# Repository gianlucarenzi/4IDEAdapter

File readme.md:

# Amiga 4 IDE Hard Parallel ATA Adapter
Created by Gianluca Renzi (C) 2019
E-Mail: <icjtqr@gmail.com>
<gianlucarenzi@eurek.it>

# What is it?
It is a simple but powerful adapter to use internally in any Amiga 1200 or Amiga 600 Computer installed in a tower-like case!
It must be connected to the IDE 44-pin interface on the motherboard to drive up to 4 ATA/ATAPI devices like Hard Drives, DVD Rom Drives and compatible drives.

This project follow the same DIY project in Aminet (search 4IDE in docs/hw) or simply check out here:

[Aminet 4IDE Readme](Aminet-4IDE/4IDE.readme)

# Software
[Aminet IDE97 Driver](http://aminet.net/driver/media/IDEfix97.lha)

[Aminet IDE97 Turbo Driver](http://aminet.net/driver/media/IDEfixTURBO.lha)

[Aminet IDE97 Patches](http://aminet.net/driver/media/IDEFix_patches.lha)

# Hardware Point-Of-View
This board has three indipendent activity leds, one for each channel. Moreover the activity leds are merged together in the motherboard so the HDD led nearby the floppy connector can be used as the only activity led.

# TODO
May be it can be useful to add a 90-degrees rise connector if the system has some sort of bus board, just to let this board flat as the motherboard.

# Images

# Whats changed?
V2.2 Added Aminet Stuff

# Licence
This entire project is available under the GNU General Public License v3 licence.
See licence.txt for more details.

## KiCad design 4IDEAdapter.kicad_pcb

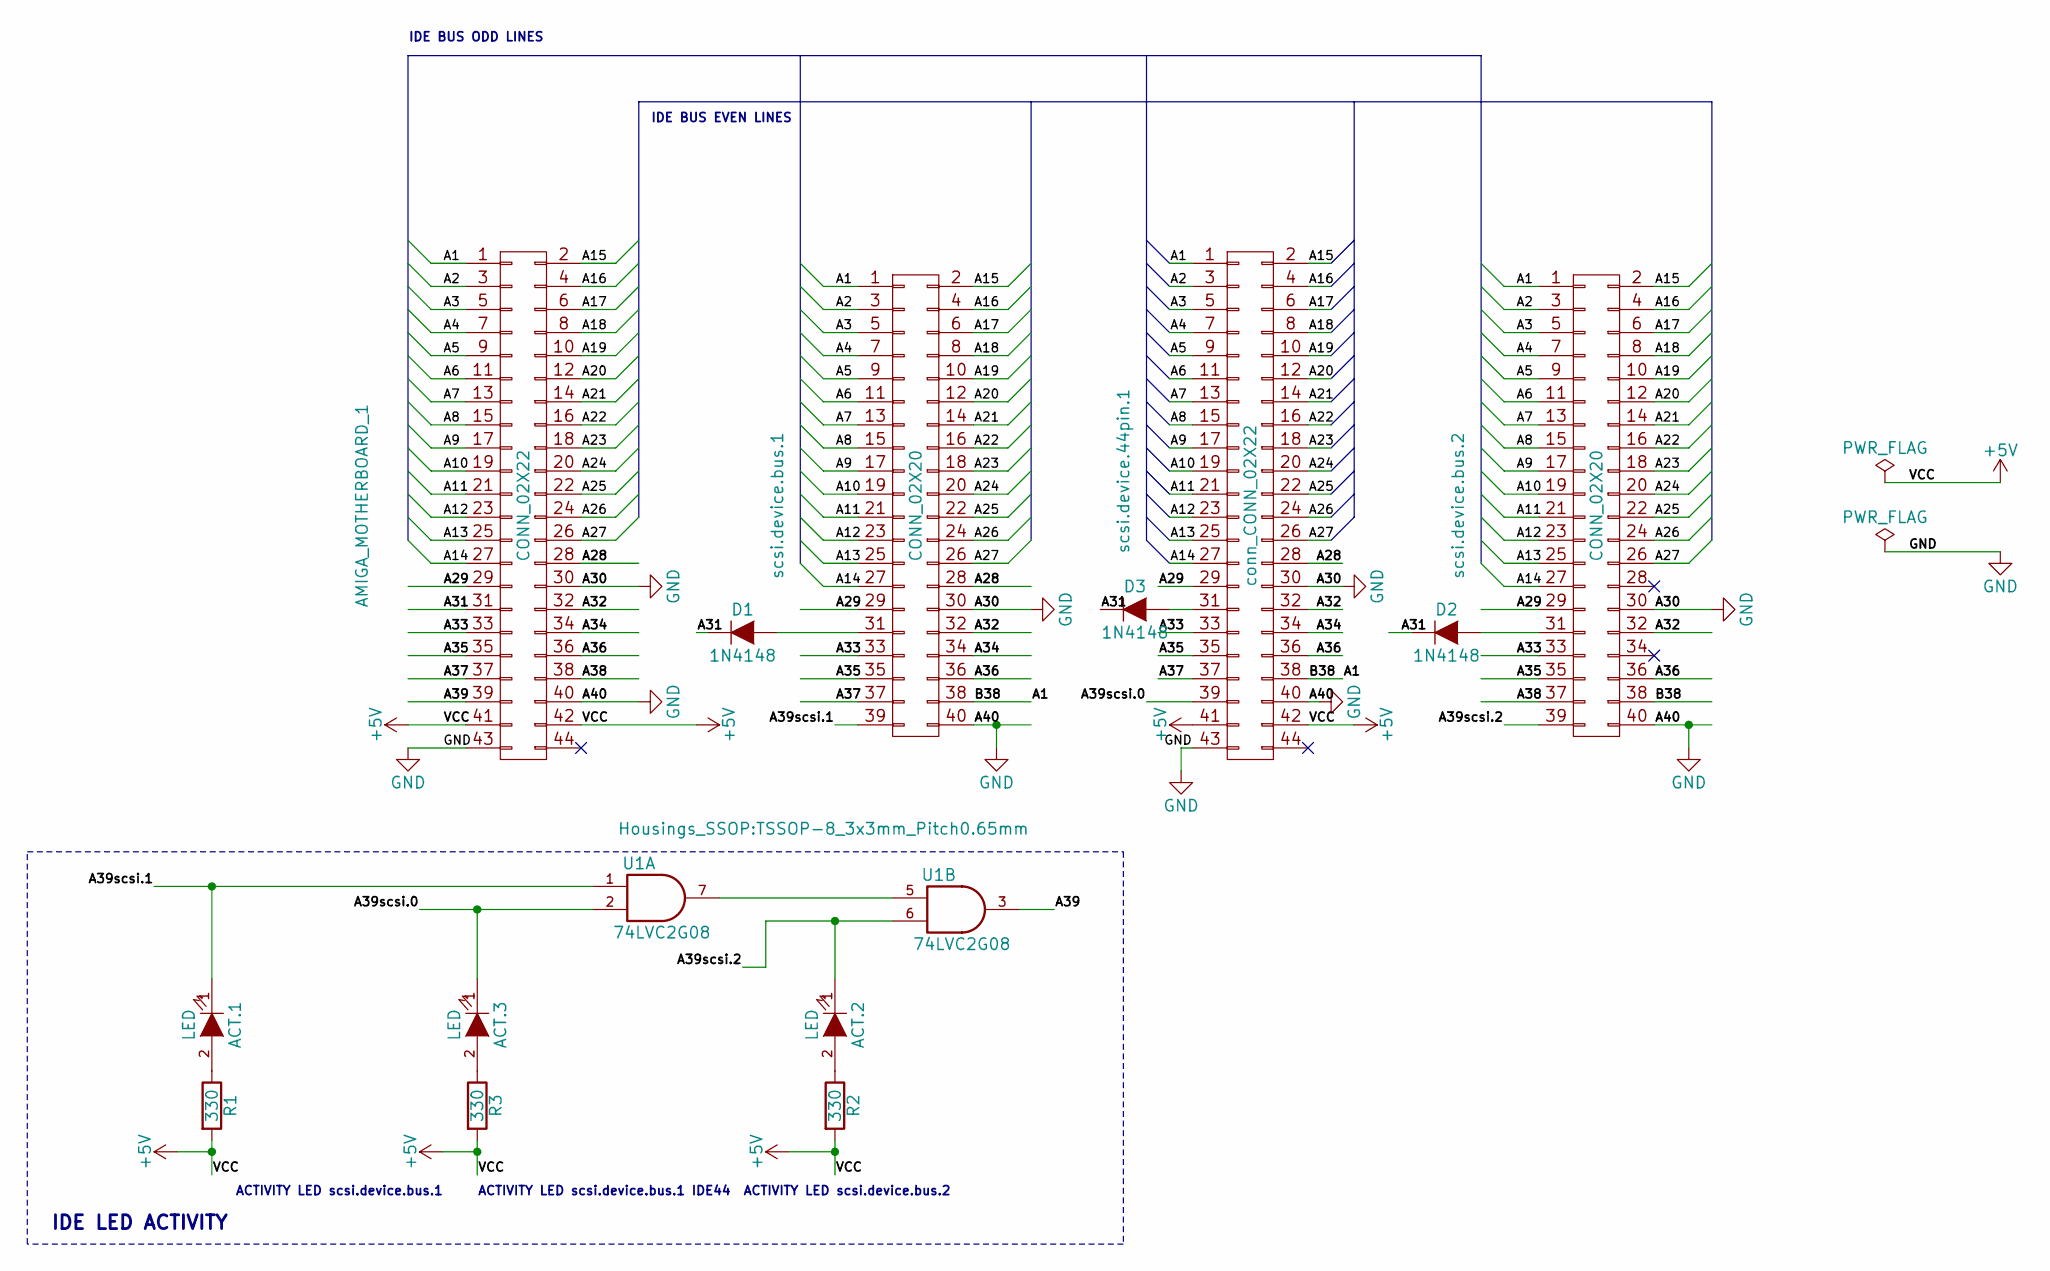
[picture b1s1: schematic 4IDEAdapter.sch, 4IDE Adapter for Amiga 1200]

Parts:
ACT.1, ACT.2, ACT.3: LED; LED_1206
AMIGA_MOTHERBOARD_1: CONN_02X22; Socket_IDC_2x22_2.00mm_PCB
D1, D2, D3: 1N4148; SMA_Handsoldering
R1, R2, R3: 330; R_1206_HandSoldering
U1: 74LVC2G08; TSSOP-8_3x3mm_Pitch0.65mm
scsi.device.44pin.1: conn_CONN_02X22; PinHeader_2x22_P2.00mm_Vertical
scsi.device.bus.1, scsi.device.bus.2: CONN_02X20; IDC-Header_2x20_P2.54mm_Vertical_Lock

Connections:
+5V: AMIGA_MOTHERBOARD_1.41, AMIGA_MOTHERBOARD_1.42, R1.2, R2.2, R3.2, U1.8 (VCC), scsi.device.44pin.1.41, scsi.device.44pin.1.42
/A1: AMIGA_MOTHERBOARD_1.1, scsi.device.44pin.1.1, scsi.device.44pin.1.38, scsi.device.bus.1.1, scsi.device.bus.1.38, scsi.device.bus.2.1, scsi.device.bus.2.38
/A2: AMIGA_MOTHERBOARD_1.3, scsi.device.44pin.1.3, scsi.device.bus.1.3, scsi.device.bus.2.3
/A3: AMIGA_MOTHERBOARD_1.5, scsi.device.44pin.1.5, scsi.device.bus.1.5, scsi.device.bus.2.5
/A4: AMIGA_MOTHERBOARD_1.7, scsi.device.44pin.1.7, scsi.device.bus.1.7, scsi.device.bus.2.7
/A5: AMIGA_MOTHERBOARD_1.9, scsi.device.44pin.1.9, scsi.device.bus.1.9, scsi.device.bus.2.9
/A6: AMIGA_MOTHERBOARD_1.11, scsi.device.44pin.1.11, scsi.device.bus.1.11, scsi.device.bus.2.11
/A7: AMIGA_MOTHERBOARD_1.13, scsi.device.44pin.1.13, scsi.device.bus.1.13, scsi.device.bus.2.13
/A8: AMIGA_MOTHERBOARD_1.15, scsi.device.44pin.1.15, scsi.device.bus.1.15, scsi.device.bus.2.15
/A9: AMIGA_MOTHERBOARD_1.17, scsi.device.44pin.1.17, scsi.device.bus.1.17, scsi.device.bus.2.17
/A10: AMIGA_MOTHERBOARD_1.19, scsi.device.44pin.1.19, scsi.device.bus.1.19, scsi.device.bus.2.19
/A11: AMIGA_MOTHERBOARD_1.21, scsi.device.44pin.1.21, scsi.device.bus.1.21, scsi.device.bus.2.21
/A12: AMIGA_MOTHERBOARD_1.23, scsi.device.44pin.1.23, scsi.device.bus.1.23, scsi.device.bus.2.23
/A13: AMIGA_MOTHERBOARD_1.25, scsi.device.44pin.1.25, scsi.device.bus.1.25, scsi.device.bus.2.25
/A14: AMIGA_MOTHERBOARD_1.27, scsi.device.44pin.1.27, scsi.device.bus.1.27, scsi.device.bus.2.27
/A15: AMIGA_MOTHERBOARD_1.2, scsi.device.44pin.1.2, scsi.device.bus.1.2, scsi.device.bus.2.2
/A16: AMIGA_MOTHERBOARD_1.4, scsi.device.44pin.1.4, scsi.device.bus.1.4, scsi.device.bus.2.4
/A17: AMIGA_MOTHERBOARD_1.6, scsi.device.44pin.1.6, scsi.device.bus.1.6, scsi.device.bus.2.6
/A18: AMIGA_MOTHERBOARD_1.8, scsi.device.44pin.1.8, scsi.device.bus.1.8, scsi.device.bus.2.8
/A19: AMIGA_MOTHERBOARD_1.10, scsi.device.44pin.1.10, scsi.device.bus.1.10, scsi.device.bus.2.10
/A20: AMIGA_MOTHERBOARD_1.12, scsi.device.44pin.1.12, scsi.device.bus.1.12, scsi.device.bus.2.12
/A21: AMIGA_MOTHERBOARD_1.14, scsi.device.44pin.1.14, scsi.device.bus.1.14, scsi.device.bus.2.14
/A22: AMIGA_MOTHERBOARD_1.16, scsi.device.44pin.1.16, scsi.device.bus.1.16, scsi.device.bus.2.16
/A23: AMIGA_MOTHERBOARD_1.18, scsi.device.44pin.1.18, scsi.device.bus.1.18, scsi.device.bus.2.18
/A24: AMIGA_MOTHERBOARD_1.20, scsi.device.44pin.1.20, scsi.device.bus.1.20, scsi.device.bus.2.20
/A25: AMIGA_MOTHERBOARD_1.22, scsi.device.44pin.1.22, scsi.device.bus.1.22, scsi.device.bus.2.22
/A26: AMIGA_MOTHERBOARD_1.24, scsi.device.44pin.1.24, scsi.device.bus.1.24, scsi.device.bus.2.24
/A27: AMIGA_MOTHERBOARD_1.26, scsi.device.44pin.1.26, scsi.device.bus.1.26, scsi.device.bus.2.26
/A28: AMIGA_MOTHERBOARD_1.28, scsi.device.44pin.1.28, scsi.device.bus.1.28
/A29: AMIGA_MOTHERBOARD_1.29, scsi.device.44pin.1.29, scsi.device.bus.1.29, scsi.device.bus.2.29
/A31: AMIGA_MOTHERBOARD_1.31, D1.1 (K), D2.1 (K), D3.1 (K)
/A32: AMIGA_MOTHERBOARD_1.32, scsi.device.44pin.1.32, scsi.device.bus.1.32, scsi.device.bus.2.32
/A33: AMIGA_MOTHERBOARD_1.33, scsi.device.44pin.1.33, scsi.device.bus.1.33, scsi.device.bus.2.33
/A34: AMIGA_MOTHERBOARD_1.34, scsi.device.44pin.1.34, scsi.device.bus.1.34
/A35: AMIGA_MOTHERBOARD_1.35, scsi.device.44pin.1.35, scsi.device.bus.1.35, scsi.device.bus.2.35
/A36: AMIGA_MOTHERBOARD_1.36, scsi.device.44pin.1.36, scsi.device.bus.1.36, scsi.device.bus.2.36
/A37: AMIGA_MOTHERBOARD_1.37, scsi.device.44pin.1.37, scsi.device.bus.1.37
/A38: AMIGA_MOTHERBOARD_1.38, scsi.device.bus.2.37
/A39: AMIGA_MOTHERBOARD_1.39, U1.3
/A39scsi.0: ACT.3.1 (K), U1.2, scsi.device.44pin.1.39
/A39scsi.1: ACT.1.1 (K), U1.1, scsi.device.bus.1.39
/A39scsi.2: ACT.2.1 (K), U1.6, scsi.device.bus.2.39
GND: AMIGA_MOTHERBOARD_1.30, AMIGA_MOTHERBOARD_1.40, AMIGA_MOTHERBOARD_1.43, U1.4 (GND), scsi.device.44pin.1.30, scsi.device.44pin.1.40, scsi.device.44pin.1.43, scsi.device.bus.1.30, scsi.device.bus.1.40, scsi.device.bus.2.30, scsi.device.bus.2.40
unnamed: ACT.1.2 (A), R1.1
unnamed: ACT.2.2 (A), R2.1
unnamed: ACT.3.2 (A), R3.1
unnamed: D1.2 (A), scsi.device.bus.1.31
unnamed: D2.2 (A), scsi.device.bus.2.31
unnamed: D3.2 (A), scsi.device.44pin.1.31
unnamed: U1.5, U1.7

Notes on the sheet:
IDE BUS ODD LINES
IDE BUS EVEN LINES
ACTIVITY LED scsi.device.bus.1
ACTIVITY LED scsi.device.bus.2
ACTIVITY LED scsi.device.bus.1 IDE44
IDE LED ACTIVITY

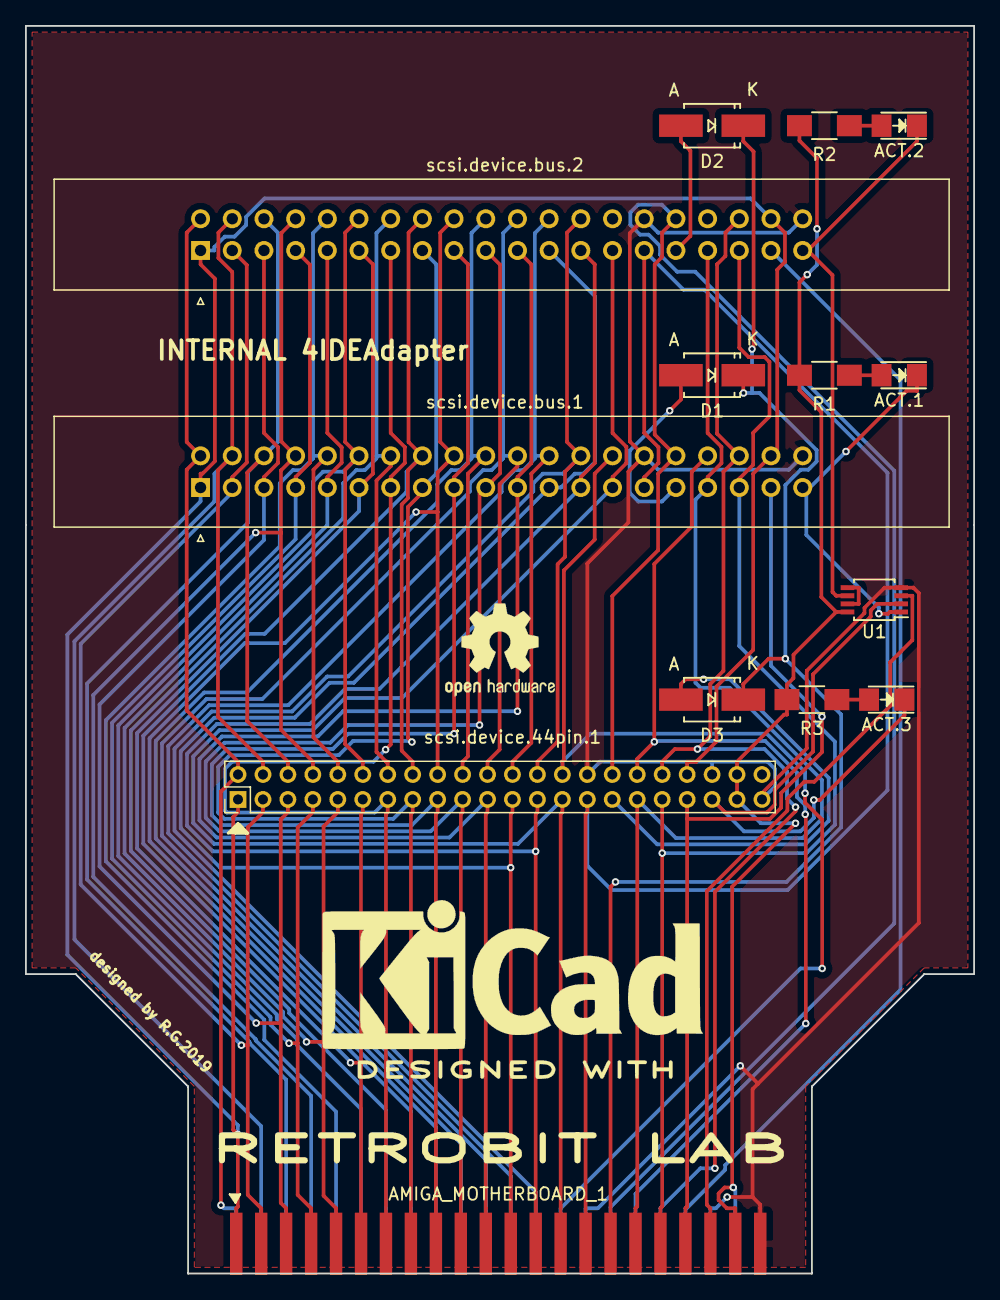
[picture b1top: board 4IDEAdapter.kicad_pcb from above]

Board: 2 copper layers, 76.0 x 100.0 mm, 15 parts (0 on the bottom side), 50 nets.

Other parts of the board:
WBLOGO: KiCad-Logo2_12mm_SilkScreen

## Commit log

2019-03-01 first import into GitHub
2019-03-01 updated path
2019-03-01 removed
2019-03-01 added another IDE 44 pin port scsi.device.0 in parallel. ONE at TIME
2019-03-01 added a second ide port 44 pin
2019-03-01 added schematics and rules for FreeRouting
2019-03-02 Updated connectors
    The IDE44 pin connector was wrong. Due to the complexity of having 3
    connectors on board the size of the board need to be increased. Now it
    is almost like a Credit Card Size. It needs an Amiga 1200 or Amiga 600
    placed into a TowerCase and *NOT TOO NEAR* to the bottom of the case...
    But if you need a 4 devices connected, for sure the default case has not
    accomplishes that!
2019-03-02 added license
2019-03-02 added activity led management
2019-03-02 Added Aminet Files
2019-03-02 added Aminet Link
2019-03-02 modified path
2019-03-18 Added Aminet driver links
2019-03-18 Better links?
2019-03-18 Another way link
2019-03-18 no white spaces
2019-10-12 Modified silkscreen
2025-11-01 RetroBitLab library
